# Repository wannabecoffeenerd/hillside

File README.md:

# Hillside View Ergonomic Keyboard

3x6                       |  3x5
:-------------------------:|:-------------------------:
  |  

The HillSideView (HSV) is a modified version of the [Hillside 46](https://github.com/mmccoyd/hillside). It is a 
 wireless (or wired) [40%](https://deskthority.net/wiki/40%25) 
 split-[ergonomic](https://deskthority.net/wiki/Ergonomic_keyboard) 
 keyboard with a 
 [column-stagger](https://deskthority.net/wiki/Staggering#Columnar_layout) 3x6+5 or a 3x5+5 layout.

The main features that the HSV adds over the Hillside 46 are:
- [nice!view](https://github.com/getkeops/keops/tree/main) e-paper display for better battery life
- Cleaner outer pinky column cut-off
- Support for a cirque trackpad with an FFC connector on the PCB itself
- Case design with support for large 750-3000 mAh batteries under the PCB
- Magnetic tenting stand with the case
- Under PCB mount for the MCU for a cleaner top display mounting

The HSV has optional factory parts soldering (PCBA) except for the switches, MCU, display, TRRS, LEDs, battery switch, and optional hotswap sockets.

Other features of the HSV are:

- Choc-spaced keys, aggressive stagger, five thumb keys
- Break-off outer pinkie column
- Tenting puck support
- QMK and wireless ZMK firmware
- Nice!nano battery power switch
- Encoder support
- Underglow from four or five SK6812-MINI-Es
- Reversible PCB
- Detailed BOM and default keyboard rationale.
- SMT diodes, resistors, capacitors, and reset switch

*Keycaps*: HillSideView is _only_ suitable for choc v1 switches and keycaps based on an 18 x 17mm switch spacing, such as the [MBK](https://mkultra.click/mbk-choc-keycaps), [Lowprokb LDSA](https://lowprokb.ca/products/ldsa-low-profile-blank-keycaps) or [KLP Lamé](https://github.com/braindefender/KLP-Lame-Keycaps/). Not MX ones, nor 18 x 18mm ones such as Work Louder, nor Kailh Choc Transparent.

## Keymap

HillSideView includes ZMK Firmware
- [full size](https://github.com/mike1808/zmk-config)
- [five column](https://github.com/wannabecoffeenerd/zmk-config)

QMK firmware can be adapted from the [Hillside firmware](https://github.com/qmk/qmk_firmware/tree/master/keyboards/handwired/hillside) 

The default keymap for the five column build:

## Key Use

I expect most people will primarily use either the tucked three thumbs or the extended three (not counting the upper thumb). They can choose where the thumb arc suits them best. I find the thumb finger is best for reaching the upper thumb key; clearing the lower thumb requires some care, but it is still very useful. The middle finger also handily reaches the most tucked thumb key, as the open space is a good reference. The keys outside of the primary three thumb keys are convenient for infrequent lock layers, escape, or for use when not actively typing for things such as mute.

## Why

The main reason for this project is to make the keyboard more wireless friendly by adding the e-paper display and allowing experimenting with using a cirque trackpad (once ZMK support for it is more stable)

## Hardware and Build Guide

See the [original Hillside wiki](https://github.com/mmccoyd/hillside/wiki)
 first for PCB ordering, parts links and a build guide with pictures.

See the [HSV wiki](https://github.com/wannabecoffeenerd/HillSideView/wiki) for HSV specific
 build guide.

 ### Bill of Materials (BOM)

| **Component**                          | **Quantity per keeb** | **URL**                                                                                                 | **Source**      | **Price Per SKU** |
|----------------------------------------|-----------------------|---------------------------------------------------------------------------------------------------------|-----------------|-------------------|
| PCB                                    |                     1 | JLCPCB                                                                                                  | JLCPCB          |            10.778 |
| nice!nano                              |                     2 | https://typeractive.xyz/products/nice-nano                                                              | typeractive.xyz |                25 |
| nice!view                              |                     2 | https://typeractive.xyz/products/nice-view                                                              | typeractive.xyz |                20 |
| switches - pro pink or other (10 pack) |                     5 | https://lowprokb.ca/collections/keyboards/products/kailh-choc-low-profile-switches                      | lowprokb.ca     |                 5 |
| mill-max sockets                       |                   100 | https://www.mouser.com/ProductDetail/Mill-Max/0305-2-15-80-47-80-10-0?qs=QtQX4uD3c2Uys0ai6Tr8NQ%3D%3D   | mouser.com      |               0.1 |
| keycaps (10 pack)                      |                     5 | https://typeractive.xyz/products/mbk-keycaps                                                            | typeractive.xyz |               3.5 |
| 2x battery - 750 mAh                   |                     2 | https://typeractive.xyz/products/lithium-battery-750mah                                                 | typeractive.xyz |                 6 |
| MCU sockets - low clearance            |                     2 | https://www.mouser.com/ProductDetail/Mill-Max/310-47-132-41-001000?qs=5aG0NVq1C4z8UdNlP%252Bvotg%3D%3D  | mouser.com      |              2.17 |
| Standoffs                              |                     8 | https://www.mouser.com/ProductDetail/Wurth-Elektronik/970060244?qs=%252BEew9%252B0nqrCEb5Os0atlaA%3D%3D | mouser.com      |              0.43 |
| MCU pins                               |                    64 | https://www.mouser.com/ProductDetail/Mill-Max/3320-0-00-15-00-00-03-0?qs=s8Nb1z4Wn%2FQ16WBIwCPrTw%3D%3D | mouser.com      |              0.05 |
| power switches                         |                     2 | https://www.mouser.com/ProductDetail/CK/JS202011AQN?qs=LgMIjt8LuD%252Bmsz6wAeWWtQ%3D%3D                 | mouser.com      |             0.471 |

Some other optional parts:

| **Component**          | **Quantity per keeb** | **URL**                                              | **Source**    | **Price Per SKU** |
|------------------------|-----------------------|------------------------------------------------------|---------------|-------------------|
| battery - 110 mAh      |                     2 | https://www.aliexpress.us/item/2255800150229489.html | aliexpress.us |              1.36 |
| battery - 2000 mAh     |                     2 | https://www.aliexpress.us/item/3256803882039204.html | aliexpress.us |              5.18 |
| EC11 rotary encoders   |                   0.4 | https://www.aliexpress.us/item/2251832789732148.html | aliexpress.us |              5.08 |
| aluminum knob for EC11 |                     1 | https://www.aliexpress.us/item/3256801125707035.html | aliexpress.us |              6.85 |

 ### 3DP case

 The HSV is designed to be used with a 3D printed case. STLs for the case are [here](https://github.com/wannabecoffeenerd/HillSideView/tree/main/hillsideview46/case)

 To main design principles for the case are:
 - Ability to use a large battery mounted under the PCB and
 - Keep the top of the HSV fairly low profile for portability and ensure nothing sticks up above the keys.

 This is achieved by having an empty cavity under the PCB that allows using up to a 2000 mAh 306070 battery. This also allows for mounting the MCU on the underside of the PCB and having the nice!view display sit fairly low on top of the PCB.
 
 The case supports tenting using a magnetic tenting stand that uses 10x1 magnets in the case and 10x3 magnets in the stand. This also allows the two sides to attach magnetically for travel.

## Acknowledgments

Several keyboards have influenced this boards, primarily the
  [Hillside 46](https://github.com/mmccoyd/hillside), but also
  [Atreus](https://shop.keyboard.io/products/keyboardio-atreus),
  [Lily58](https://github.com/kata0510/Lily58),
  [Kyria](https://splitkb.com/collections/keyboard-kits/products/kyria-pcb-kit),
  [Corne](https://github.com/foostan/crkbd) and
  [Ferris](https://github.com/pierrechevalier83/ferris).

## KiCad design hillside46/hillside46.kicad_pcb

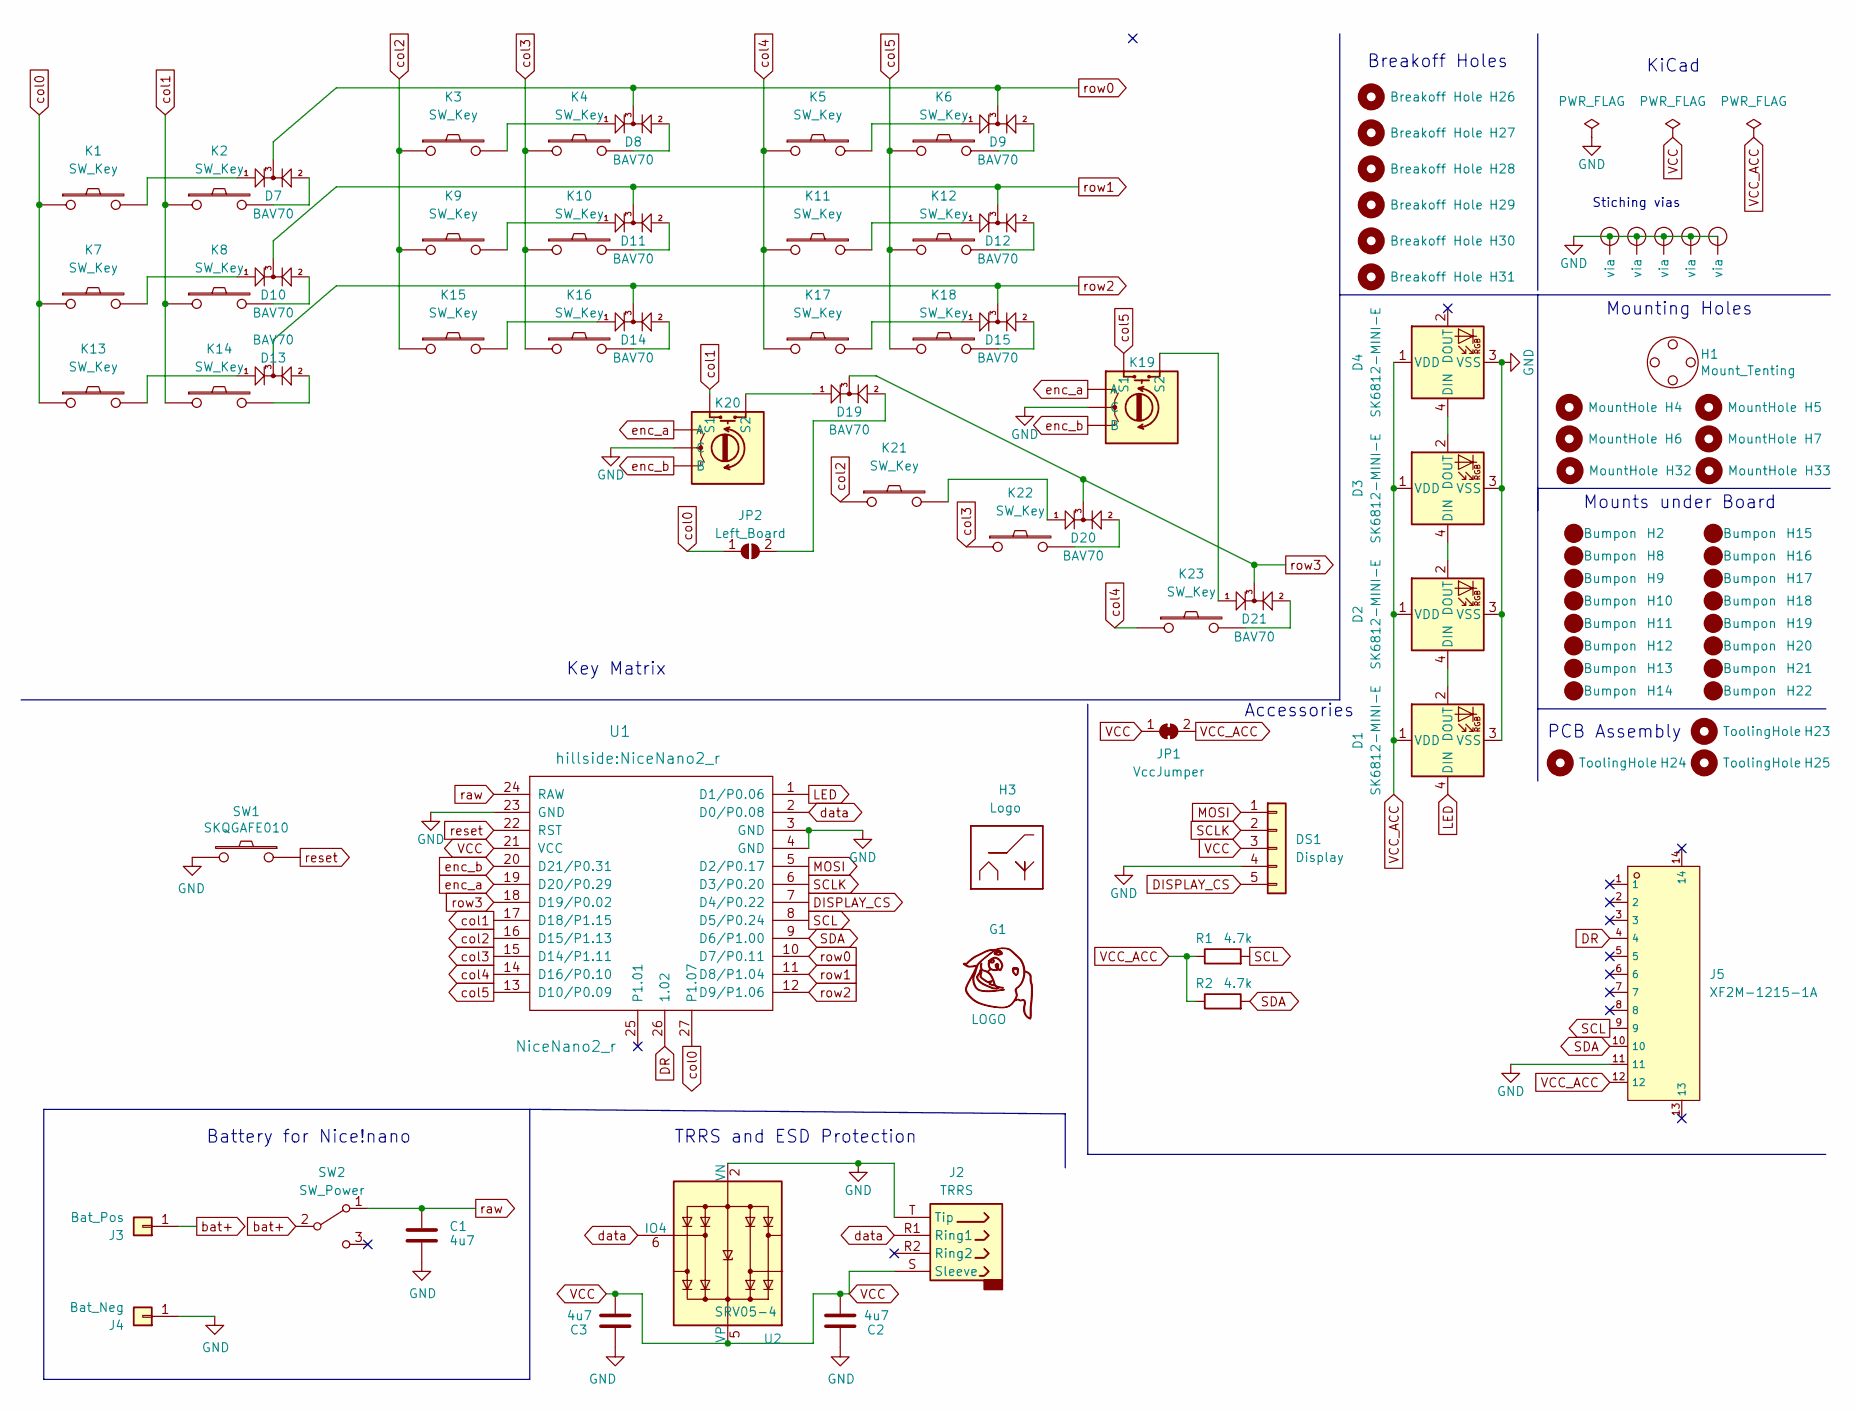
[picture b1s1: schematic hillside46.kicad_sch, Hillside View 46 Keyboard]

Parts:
C1, C2, C3: 4u7; C_0805_2012Metric; JLC Type Basic
D1, D2, D3, D4: SK6812-MINI-E
D7, D8, D9, D10, D11, D12, D13, D14, D15, D19, D20, D21: BAV70; SOT-23; LCSC C68978
DS1: Display; NiceView
G1: LOGO; wowee
H1: Mount_Tenting; Tenting_Puck
H2, H8, H9, H10, H11, H12, H13, H14, H15, H16, H17, H18, H19, H20, H21, H22: Bumpon
H3: Logo; Hillside_Logo
H4, H5, H6, H7, H32, H33: MountHole; MountingHole_2.2mm_with_PCB_insert_rings
H23, H24, H25: ToolingHole; ToolingHole_1.152mm
H26, H27, H28, H29, H30, H31: Breakoff Hole; HoleBreakoff_1mm
J2: TRRS; MJ-4PP-9
J3: Bat_Pos; 1pin_conn
J4: Bat_Neg; 1pin_conn
J5: XF2M-1215-1A; FPC-SMD_12P-P0.50_XF2M-1215-1A; PARTREV A; JLC Type Extended
JP1: VccJumper; SolderJumper-2_P1.3mm_Bridged_RoundedPad1.0x1.5mm
JP2: Left_Board; SolderJumper-2_P1.3mm_Open_TrianglePad1.0x1.5mm
K1, K2, K3, K4, K5, K6, K7, K8, K9, K10, K11, K12, K13, K14, K15, K16, K17, K18, K21, K22, K23: SW_Key; pg1350-R_hotswap
K19, K20: SW_Rotary; pg1350-DR_rotary_hotswap
R1, R2: 4.7k; R_0805_2012Metric; LCSC C17673
SW1: SKQGAFE010; SW_SPST_SKQG_WithStem; LCSC C318884
SW2: SW_Power; SW_SPDT_JS202011AQN; LCSC C221662
U1: NiceNano2_r
U2: SRV05-4; SOT-23-6_Handsoldering_threenumbered; JLC Type Basic
V1, V2, V3, V4, V5: Via; VIA-0.8mm

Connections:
DISPLAY_CS: DS1.5, U1.7 (D4/P0.22)
DR: J5.4, U1.26 (1.02)
GND: C1.2, C2.1, C3.1, D1.3 (VSS), D2.3 (VSS), D3.3 (VSS), D4.3 (VSS), DS1.4, J2.T (Tip), J4.1, J5.11, K19.C, K20.C, SW1.2, U1.3 (GND), U1.4 (GND), U1.23 (GND), U2.2 (VN), V1.1 (via), V2.1 (via), V3.1 (via), V4.1 (via), V5.1 (via)
LED: D1.4 (DIN), U1.1 (D1/P0.06)
MOSI: DS1.1, U1.5 (D2/P0.17)
unnamed: D1.2 (DOUT), D2.4 (DIN)
unnamed: D2.2 (DOUT), D3.4 (DIN)
unnamed: D3.2 (DOUT), D4.4 (DIN)
unnamed: D7.1 (A1), K1.2
unnamed: D7.2 (A2), K2.2
unnamed: D8.1 (A1), K3.2
unnamed: D8.2 (A2), K4.2
unnamed: D9.1 (A1), K5.2
unnamed: D9.2 (A2), K6.2
unnamed: D10.1 (A1), K7.2
unnamed: D10.2 (A2), K8.2
unnamed: D11.1 (A1), K9.2
unnamed: D11.2 (A2), K10.2
unnamed: D12.1 (A1), K11.2
unnamed: D12.2 (A2), K12.2
unnamed: D13.1 (A1), K13.2
unnamed: D13.2 (A2), K14.2
unnamed: D14.1 (A1), K15.2
unnamed: D14.2 (A2), K16.2
unnamed: D15.1 (A1), K17.2
unnamed: D15.2 (A2), K18.2
unnamed: D19.1 (A1), K20.S2
unnamed: D19.2 (A2), JP2.2 (B)
unnamed: D20.1 (A1), K21.2
unnamed: D20.2 (A2), K22.2
unnamed: D21.1 (A1), K19.S2
unnamed: D21.2 (A2), K23.2
SCL: J5.9, R1.2, U1.8 (D5/P0.24)
SCLK: DS1.2, U1.6 (D3/P0.20)
SDA: J5.10, R2.2, U1.9 (D6/P1.00)
VCC: C2.2, C3.2, DS1.3, J2.S (Sleeve), JP1.1 (A), U1.21 (VCC), U2.5 (VP)
VCC_ACC: D1.1 (VDD), D2.1 (VDD), D3.1 (VDD), D4.1 (VDD), J5.12, JP1.2 (B), R1.1, R2.1
bat+: J3.1, SW2.2 (B)
col0: JP2.1 (A), K1.1, K7.1, K13.1, U1.27 (P1.07)
col1: K2.1, K8.1, K14.1, K20.S1, U1.17 (D18/P1.15)
col2: K3.1, K9.1, K15.1, K21.1, U1.16 (D15/P1.13)
col3: K4.1, K10.1, K16.1, K22.1, U1.15 (D14/P1.11)
col4: K5.1, K11.1, K17.1, K23.1, U1.14 (D16/P0.10)
col5: K6.1, K12.1, K18.1, K19.S1, U1.13 (D10/P0.09)
data: J2.R1 (Ring1), U1.2 (D0/P0.08), U2.6 (IO4)
enc_a: K19.A, K20.A, U1.19 (D20/P0.29)
enc_b: K19.B, K20.B, U1.20 (D21/P0.31)
raw: C1.1, SW2.1 (A), U1.24 (RAW)
reset: SW1.1, U1.22 (RST)
row0: D7.3 (K), D8.3 (K), D9.3 (K), U1.10 (D7/P0.11)
row1: D10.3 (K), D11.3 (K), D12.3 (K), U1.11 (D8/P1.04)
row2: D13.3 (K), D14.3 (K), D15.3 (K), U1.12 (D9/P1.06)
row3: D19.3 (K), D20.3 (K), D21.3 (K), U1.18 (D19/P0.02)

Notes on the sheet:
KiCad
Mounting Holes
Key Matrix
Battery for Nice!nano
TRRS and ESD Protection
PCB Assembly
Stiching vias
Breakoff Holes
Mounts under Board
Accessories

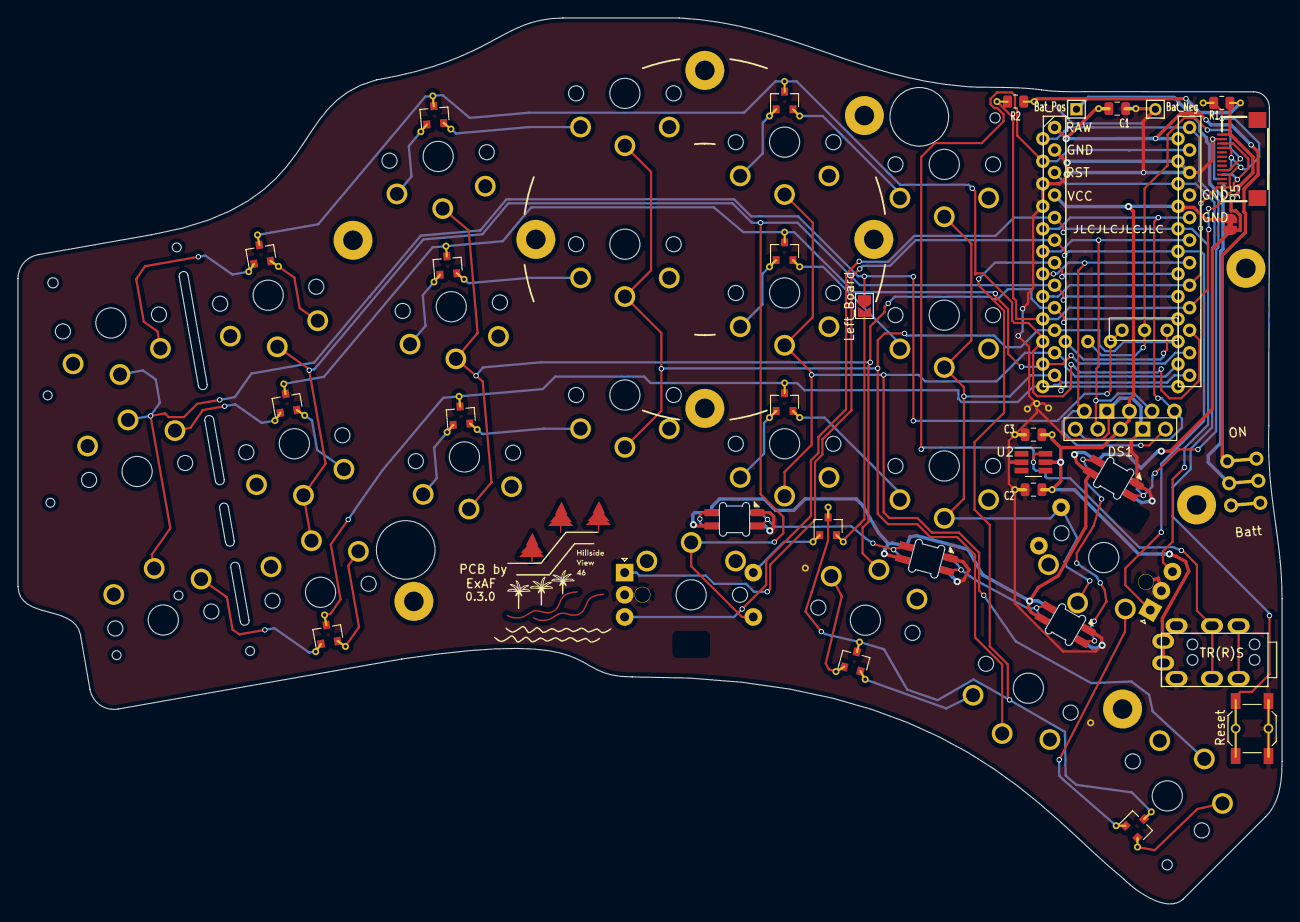
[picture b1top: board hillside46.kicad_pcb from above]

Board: 2 copper layers, 142.5 x 99.9 mm, 94 parts (1 on the bottom side), 53 nets.

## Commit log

2022-10-10 Adding nice view footprints and removing old haptic buzzer, I2C pullup resistors and all LEDs
2022-10-17 Adding cirque connector to the under side of the PCB for right side assembly
2022-10-17 Adding some JLCPCB part numbers
2022-10-17 Updating ffc footprint to not require unused pads to be connected
2022-10-18 Denoting ffc connector as SMD for PCBA
2022-10-19 Updating FFC connector to use the same footprint as JLCPCB part and rotating by 180 degrees to orient correctly
2022-10-19 Updating pcb art
2022-10-21 Updating library paths to project relative paths
2022-12-18 Move switch, flip the copper on DS
    Move the switch to the side of the PCB to make it easier to swtich.
    Flip the copper layer for the display connector.
2023-01-16 Updating output step file
2023-01-30 Connecting the data ready pin
2023-05-15 Flipping nice nano vias for bottom mount, removed I2C headers, moved edge cut closer to the nice nano edge
2023-05-22 Updating pinky column cutouts to be aligned with pinky switches
2023-06-04 Adding mounting holes for the display cover
2023-06-04 Fixing warning with overlapping silk screen text
2023-07-28 Updating license and readme
2023-07-28 Adding build images
2023-07-28 Adding images to readme
2023-11-04 Adding case STLs
2023-11-04 Cleaning up repo
2023-11-04 Updating README.md to include case link and fixing images
2023-11-04 Renaming kicad project to hillsideview46
2023-11-04 Updating kibot yaml
2023-11-04 Changing kibot version to v2_k6
2023-11-04 Changing kibot version to v2_k6_1_6_2
2023-11-04 Changing to checkout v3
2023-11-04 Changing kibot version to v2_k6_1_6_0
2023-11-04 Changing kibot version to v2_k6_1_5_1
2023-11-04 Changing kibot version to v2_k7
2023-11-04 Revert "Changing kibot version to v2_k6_1_6_2"
    This reverts commit 9e90bd8d6ef18eaec0f0a4ce2b2a7dee6192a53b.
2023-11-04 Adding some more images
2023-11-05 Updating 3x5 klp lame image
2023-11-05 More documentation and adding BOM
2023-11-05 Some typo fixes
2024-08-07 Updating case STLs and adding cirque trackpad holder
2024-08-18 Add alternative case for hillsideview46
2024-09-01 Add the Fusion 360 project for the hillsideview46 alternative case
2024-10-07 Add alternative case for bottom mounted components
    Some users prefer to solder the power switch and FFC connector
    to the bottom of the PCB. This commits adds compatible versions of the
    alternative case.
